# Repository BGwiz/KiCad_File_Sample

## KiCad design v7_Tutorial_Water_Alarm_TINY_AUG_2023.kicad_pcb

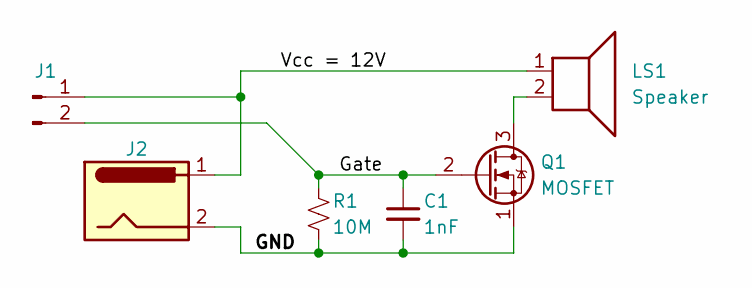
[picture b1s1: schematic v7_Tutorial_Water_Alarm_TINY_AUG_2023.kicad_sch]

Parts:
C1: 1nF; C_Disc_D4.3mm_W1.9mm_P5.00mm; Part Number BC2659CT-ND
J1: Conn_01x02_Pin; TerminalBlock_2057-EBBA-02-C-SS-BU-ND__EBBA-02-C-SS-BU__1x0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; Part Number 2057-EBBA-02-C-SS-BU-ND
J2: Jack-DC; BarrelJack_CP-037A-ND_PJ-037A_Horizontal; Part Number CP-037A-ND
LS1: Speaker; Buzzer_668-1652-ND_AI-3035-TT-12V-R___D30.4mm_P15.0mm; Part Number 668-1652-ND
Q1: MOSFET; TO-92_Inline; Part Number 2N7000BU-ND
R1: 10M; R_Axial_DIN0204_L3.6mm_D1.6mm_P2.54mm_Vertical; Part Number CF18JT10M0CT-ND

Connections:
/GND: C1.2, J2.2, Q1.1 (S), R1.2
/Gate: C1.1, J1.2, Q1.2 (G), R1.1
/Vcc = 12V: J1.1, J2.1, LS1.1
unnamed: LS1.2, Q1.3 (D)

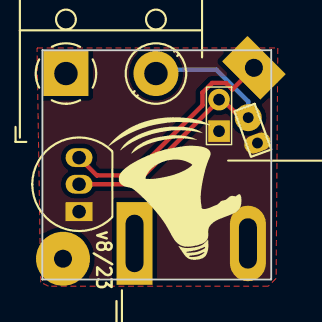
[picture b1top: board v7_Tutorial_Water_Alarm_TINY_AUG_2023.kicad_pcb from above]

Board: 2 copper layers, 12.7 x 12.7 mm, 6 parts (1 on the bottom side), 4 nets.
